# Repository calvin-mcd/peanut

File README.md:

# peanut

alice like 30% inspired by littol and tsuru. Case design, layout and concept by calumwri. Pcb by calvin0563

## Layout

[Link](http://www.keyboard-layout-editor.com/#/gists/5c7a74c8b3bbc1b4ac3f81c209dc5aab)

## Case & Plate

Case and plate files are included in the respective folder.

The case requires m2x3mm heat set inserts and 3mm silicone inserts for the feet.

## Firmware

Flash file and source code included in the respective folder.

## Pictures

## Todo

- [X] order & test pcb
- [X] test case
- [X] create firmware

## Disclaimer

This PCB has been fully tested and confirmed to work. The members of the PCB development team are however not liable if you end up with a non-functional pcb. Order at your own risk. Support will not be provided but pull requests will be reviewed and possibly accepted.

## License

This project is released under the GPL v3 License. Please refer to the LICENCE file.

## Credits

As always big thanks to the many people who helped me and inspired this board!

Any questions, contact Calvin0563 on Discord.

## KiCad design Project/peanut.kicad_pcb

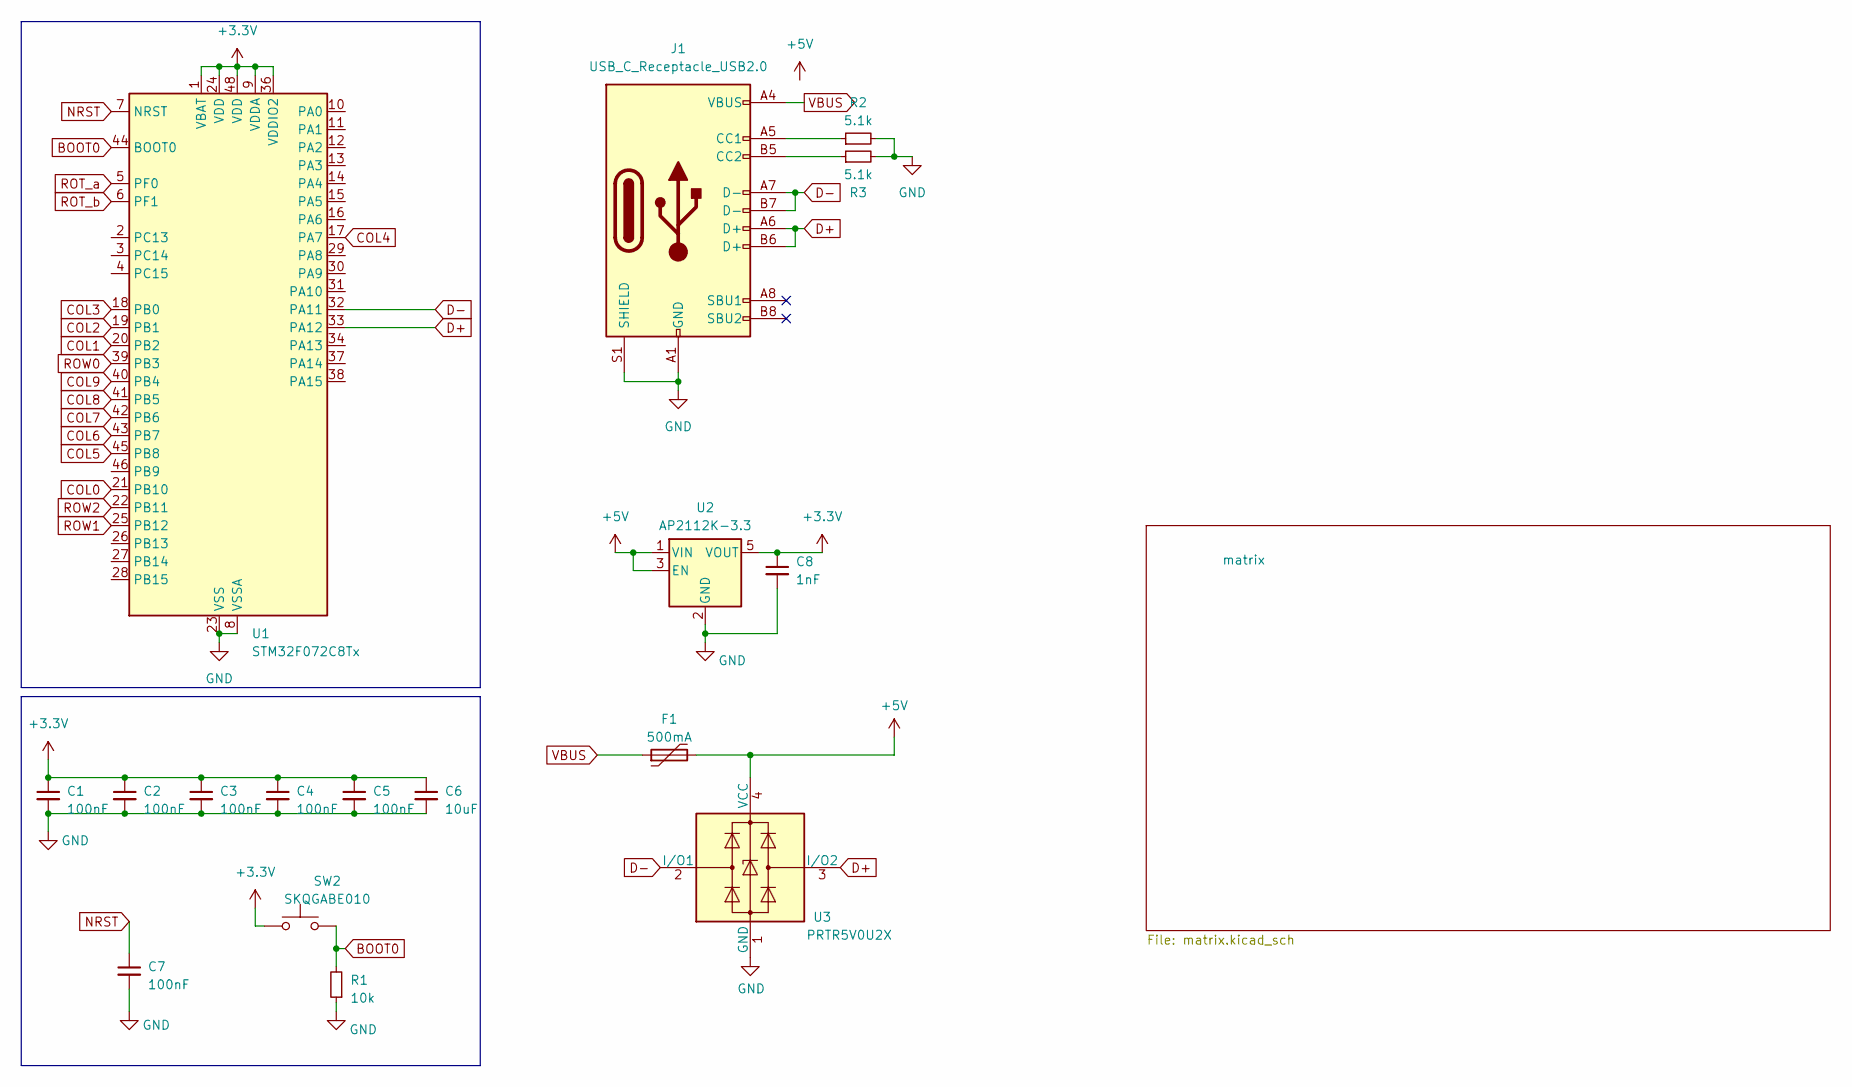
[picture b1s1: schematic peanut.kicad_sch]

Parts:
C1, C2, C3, C4, C5, C7: 100nF; C_0805_2012Metric_Pad1.18x1.45mm_HandSolder
C6: 10uF; C_0805_2012Metric_Pad1.18x1.45mm_HandSolder
C8: 1nF; C_0805_2012Metric_Pad1.18x1.45mm_HandSolder; LCSC Part Number C129637
F1: 500mA; Fuse_1206_3216Metric_Pad1.42x1.75mm_HandSolder; LCSC C135341
J1: USB_C_Receptacle_USB2.0; USB_C_Receptacle_HRO_TYPE-C-31-M-12; LCSC Part Number C3001293
R1: 10k; R_0805_2012Metric_Pad1.20x1.40mm_HandSolder
R2, R3: 5.1k; R_0805_2012Metric_Pad1.20x1.40mm_HandSolder
SW2: SKQGABE010; SW_Push_SPST_NO_Alps_SKRK; LCSC C115351
U1: STM32F072C8Tx; LQFP-48_7x7mm_P0.5mm
U2: AP2112K-3.3; SOT-23-5_HandSoldering; MPN AP2112K-3.3; LCSC Part Number C3021085
U3: PRTR5V0U2X; SOT-143_Handsoldering; LCSC C2827688

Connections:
+3.3V: C1.1, C2.1, C3.1, C4.1, C5.1, C6.1, C8.1, SW2.1, U1.1 (VBAT), U1.9 (VDDA), U1.24 (VDD), U1.36 (VDDIO2), U1.48 (VDD), U2.5 (VOUT)
+5V: F1.2, U2.1 (VIN), U2.3 (EN), U3.4 (VCC)
BOOT0: R1.2, SW2.2, U1.44 (BOOT0)
COL0: U1.21 (PB10); also elsewhere on the board
COL1: U1.20 (PB2); also elsewhere on the board
COL2: U1.19 (PB1); also elsewhere on the board
COL3: U1.18 (PB0); also elsewhere on the board
COL4: U1.17 (PA7); also elsewhere on the board
COL5: U1.45 (PB8); also elsewhere on the board
COL6: U1.43 (PB7); also elsewhere on the board
COL7: U1.42 (PB6); also elsewhere on the board
COL8: U1.41 (PB5); also elsewhere on the board
COL9: U1.40 (PB4); also elsewhere on the board
D+: J1.A6 (D+), J1.B6 (D+), U1.33 (PA12), U3.3 (I/O2)
D-: J1.A7 (D-), J1.B7 (D-), U1.32 (PA11), U3.2 (I/O1)
GND: C1.2, C2.2, C3.2, C4.2, C5.2, C6.2, C7.2, C8.2, J1.A1 (GND), J1.A12 (GND), J1.B1 (GND), J1.B12 (GND), J1.S1 (SHIELD), R1.1, R2.2, R3.2, U1.8 (VSSA), U1.23 (VSS), U1.35 (VSS), U1.47 (VSS), U2.2 (GND), U3.1 (GND); also elsewhere on the board
NRST: C7.1, U1.7 (NRST)
unnamed: J1.A5 (CC1), R2.1
unnamed: J1.B5 (CC2), R3.1
ROT_a: U1.5 (PF0); also elsewhere on the board
ROT_b: U1.6 (PF1); also elsewhere on the board
ROW0: U1.39 (PB3); also elsewhere on the board
ROW1: U1.25 (PB12); also elsewhere on the board
ROW3: U1.22 (PB11); also elsewhere on the board
VBUS: F1.1, J1.A4 (VBUS), J1.A9 (VBUS), J1.B4 (VBUS), J1.B9 (VBUS)

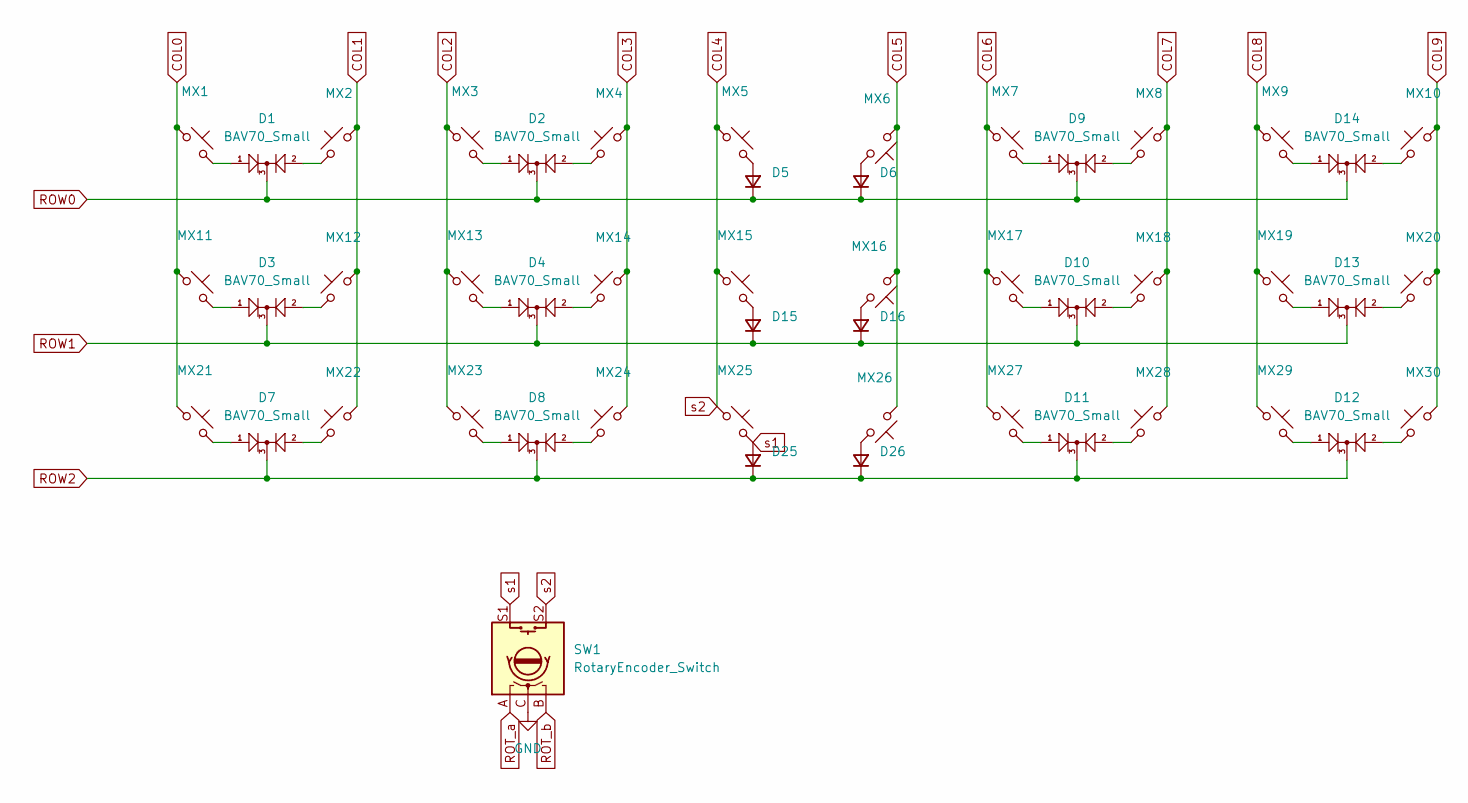
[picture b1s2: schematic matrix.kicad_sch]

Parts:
D1, D2, D3, D4, D7, D8, D9, D10, D11, D12, D13, D14: BAV70_Small; SOT-23
D5, D6, D15, D16, D25, D26: D_Small; D_SOD-123F
MX1, MX10: MX_SW_HS; SW_MX_HS_CPG151101S11_1.5u
MX2, MX3, MX4, MX5, MX6, MX7, MX8, MX9, MX12, MX13, MX14, MX15, MX16, MX17, MX18, MX19, MX21, MX22, MX23, MX24, MX25, MX27, MX28, MX29, MX30: MX_SW_HS; SW_MX_HS_CPG151101S11_1u
MX11, MX20: MX_SW_HS; SW_MX_HS_CPG151101S11_1.25u
MX26: MX_SW_HS; SW_MX_HS_CPG151101S11_1.75u
SW1: RotaryEncoder_Switch; ROT_Alps_EC11E-Switch

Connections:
COL0: MX1.1, MX11.1, MX21.1; also elsewhere on the board
COL1: MX2.2, MX12.2, MX22.2; also elsewhere on the board
COL2: MX3.1, MX13.1, MX23.1; also elsewhere on the board
COL3: MX4.2, MX14.2, MX24.2; also elsewhere on the board
COL4: MX5.1, MX15.1, MX25.1, SW1.S2; also elsewhere on the board
COL5: MX6.1, MX16.1, MX26.1; also elsewhere on the board
COL6: MX7.1, MX17.1, MX27.1; also elsewhere on the board
COL7: MX8.2, MX18.2, MX28.2; also elsewhere on the board
COL8: MX9.1, MX19.1, MX29.1; also elsewhere on the board
COL9: MX10.2, MX20.2, MX30.2; also elsewhere on the board
GND: SW1.C; also elsewhere on the board
unnamed: D1.1 (A1), MX1.2
unnamed: D1.2 (A2), MX2.1
unnamed: D2.1 (A1), MX3.2
unnamed: D2.2 (A2), MX4.1
unnamed: D3.1 (A1), MX11.2
unnamed: D3.2 (A2), MX12.1
unnamed: D4.1 (A1), MX13.2
unnamed: D4.2 (A2), MX14.1
unnamed: D5.2 (A), MX5.2
unnamed: D6.2 (A), MX6.2
unnamed: D7.1 (A1), MX21.2
unnamed: D7.2 (A2), MX22.1
unnamed: D8.1 (A1), MX23.2
unnamed: D8.2 (A2), MX24.1
unnamed: D9.1 (A1), MX7.2
unnamed: D9.2 (A2), MX8.1
unnamed: D10.1 (A1), MX17.2
unnamed: D10.2 (A2), MX18.1
unnamed: D11.1 (A1), MX27.2
unnamed: D11.2 (A2), MX28.1
unnamed: D12.1 (A1), MX29.2
unnamed: D12.2 (A2), MX30.1
unnamed: D13.1 (A1), MX19.2
unnamed: D13.2 (A2), MX20.1
unnamed: D14.1 (A1), MX9.2
unnamed: D14.2 (A2), MX10.1
unnamed: D15.2 (A), MX15.2
unnamed: D16.2 (A), MX16.2
unnamed: D26.2 (A), MX26.2
ROT_a: SW1.A; also elsewhere on the board
ROT_b: SW1.B; also elsewhere on the board
ROW0: D1.3 (K), D2.3 (K), D5.1 (K), D6.1 (K), D9.3 (K), D14.3 (K); also elsewhere on the board
ROW1: D3.3 (K), D4.3 (K), D10.3 (K), D13.3 (K), D15.1 (K), D16.1 (K); also elsewhere on the board
ROW3: D7.3 (K), D8.3 (K), D11.3 (K), D12.3 (K), D25.1 (K), D26.1 (K); also elsewhere on the board
s1: D25.2 (A), MX25.2, SW1.S1

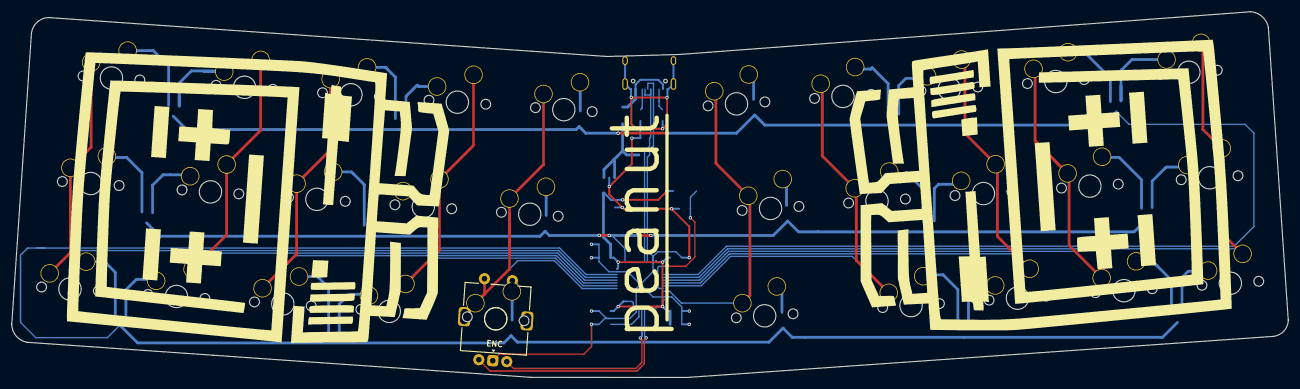
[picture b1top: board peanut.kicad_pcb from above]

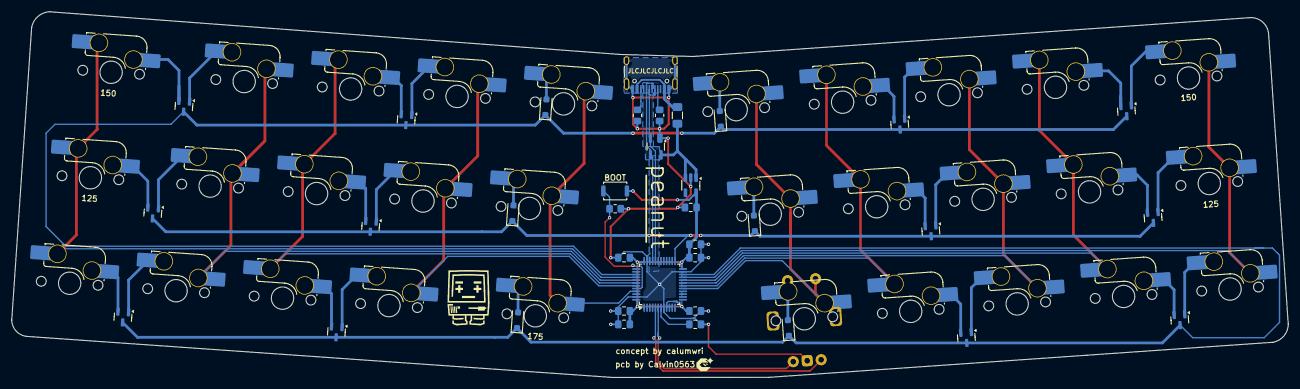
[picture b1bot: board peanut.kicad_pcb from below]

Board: 2 copper layers, 227.9 x 65.3 mm, 66 parts (65 on the bottom side), 55 nets.

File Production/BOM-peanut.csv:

Comment,Designator,Footprint,LCSC
5.1k,"R2,R3",R_0805_2012Metric_Pad1.20x1.40mm_HandSolder,C118848
1nF,C8,C_0805_2012Metric_Pad1.18x1.45mm_HandSolder,C7419428 
500mA,F1,Fuse_1206_3216Metric_Pad1.42x1.75mm_HandSolder,C135341
10uF,C6,C_0805_2012Metric_Pad1.18x1.45mm_HandSolder,C15850
10k,R1,R_0805_2012Metric_Pad1.20x1.40mm_HandSolder,C17414
100nF,"C1,C2,C3,C4,C5,C7",C_0805_2012Metric_Pad1.18x1.45mm_HandSolder,C28233
PRTR5V0U2X,U3,SOT-143_Handsoldering,C2827688
USB_C_Receptacle_USB2.0,J1,USB_C_Receptacle_HRO_TYPE-C-31-M-12,C165948
AP2112K-3.3,U2,SOT-23-5_HandSoldering,C3021085
BAV70_Small,"D1,D10,D11,D12,D13,D14,D2,D3,D4,D7,D8,D9",SOT-23,C5184417
SKQGABE010,SW2,SW_Push_SPST_NO_Alps_SKRK,C561519
D_Small,"D15,D16,D25,D26,D5,D6",D_SOD-123F,C64898
STM32F072C8Tx,U1,LQFP-48_7x7mm_P0.5mm,C80488

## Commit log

2024-09-04 initalise
2024-09-05 added case renders
2024-09-08 firmware
2024-09-18 update firmware
2024-10-01 case & plate file added, readme update
2024-10-05 image update
